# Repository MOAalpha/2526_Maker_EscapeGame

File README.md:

Projet de GHERRAS M.A., dans le cadre de l'option MAKER 2526.
# **<u>EscapeGame</u>**

Ceci est un projet personnel. L'objectif est de créer une boîte avec différentes énigmes, en mettant en oeuvre différentes compétences apprises, entre la Conception Assistée par Ordinateur (CAO) jusqu'à la fabrication d'un PCB.

## Synopsis

*Une épidémie ravage le monde. Personne n'est à l'abri. Environ 10 000 000 de personnes succombent chaque seconde. Le virus possède une forte volatilité et tue en quelques jours. Le docteur Frank MaBoule, après avoir utilisé sa fille comme cobaye,  a créé un remède. Sa fille ayant succombé, il décida de cacher son remède.Sauriez-vous être le héros qui sauvera ~~le monde~~ votre peau ? Voici les épreuves qui vous attendent :*

### 1. FIND A CODE 
Pour ouvrir la première porte, il faut résoudre une énigme très classique consistant à reconstituer une séquence sur un damier de 4x4 symbolisé par 16 écrans.

### 2. DRESS or LESS 

Pour la deuxième porte, l'idée est de vêtir 3 personnages avec le bon chapeau, pull et pentalon, à l'aide de capteurs RFID. Pour cela, une description incomplète sera fournie à travers l'écran principale.

### 3. CHOOSE THE HERO

Parmi les 3 personnages, un seul cache le remède. Vous aurez leur témoignage pour savoir qui possède le remède.

## Matériel (liste actuelle non exhaustive):

> - 1 écran 15cmx10cm tactile (moniteur principale) [de ce type-là](https://www.amazon.fr/Tactile-Fabricant-Bricolage-Internet-%C3%A9lectrique/dp/B0BWNQKWJR)
> - 16 écrans de 4x4 ?
> - Actionneurs pour portes ? 
> - PLA pour les personnages
> - tissu pour les vêtements
> - ~Capteurs RFID miniatures ?~
> - [Capteurs magnétiques, reed switchs](https://www.amazon.fr/Gebildet-interrupteurs-Plastique-Contact-Aimant/dp/B07Z4RR4QV/ref=sr_1_6?dib=eyJ2IjoiMSJ9.kGH2TBV2svDam5SUsecZEp0ydWFLr87Lerqu3hkDXa-I73LrAi6tJurhBRlbuaOspJMU1R2bbn2FAA0ulAMiDROJe-FI64w4Tjx_S1jUe9Khu_sLVSmTS067nG6PzxzhEe5ynbjlwu14H0lsywINTnsO49MUYXsK2D6I_bHxoZ03CqrzpxEMnH7ZNclkzauLTkVpxc65eaC75tjzrhDfIBqrKW-iIr1qnzNfiRqiW8g6QUxy09GzQAjlkQqSTfp91xtdCeA01pv9tRQlohX_FAPPxJ8mOdgauN9amGSbQV0.4Op6Iyob0iHGZqmOrZvQicO9HlkG0YgwPn08NIkEwyQ&dib_tag=se&keywords=reed%2Bswitch&qid=1771235277&sr=8-6&th=1)
> - *A suivre...*

## Planning prévisionnel 

| Séance                  | Action prévue |
|-------------------------|---------------|
| Lundi 16 février 2026   |  Conception des énigmes + Début schématique PCB           |
| Jeudi 19 février 2026   |     Choix des composants(Ecrans, Rasperry Pi/STM) + Suite PCB        |
| Lundi 9 mars 2026       | Début conception mécanique (Plan de la boite, portes, personnages...)              |
| Jeudi 12 mars 2026      |      Découpe laser pour la boîte et premières impressions de pièces         |
| Lundi 16 mars 2026      |    Test PCB        |
| Jeudi 19 mars 2026      |   Setup capteurs RFID + Ecrans principales              |
| Lundi 23 mars 2026      |  Améliorations + Correction             |
| Jeudi 26 mars 2026      |  Code sur STM/Rasberry Pi             |
| Lundi 30 mars 2026      |    Tests / A voir            |
| Jeudi 2 avril 2026      |    A voir            |
| Jeudi 9 avril 2026      |  Possibilité de rajouter des énigmes si tout fonctionne. / Création chatbot pour l'énigme des personnages si le temps le permet.            |
| Lundi 13 avril 2026     |   A voir            |

GANTT : (*IA MADE, for visual*)

```mermaid

gantt
    title Planning du projet (février – avril 2026)
    dateFormat  YYYY-MM-DD
    axisFormat  %d/%m

    section Conception
    Conception des énigmes + schéma PCB         :a1, 2026-02-16, 3d
    Choix composants + suite PCB                :a2, after a1, 3d

    section Mécanique
    Conception mécanique (boîte, portes, persos):b1, 2026-03-09, 4d
    Découpe laser + impressions pièces          :b2, after b1, 3d

    section Électronique
    Test PCB                                    :c1, after a2, 2d
    Setup capteurs RFID + écrans principaux     :c2, after c1, 3d

    section Développement
    Améliorations + corrections                 :d1, after c2, 3d
    Code sur STM / Raspberry Pi                 :d2, after d1, 4d

    section Tests & ajustements
    Tests généraux                              :e1, after d2, 3d
    Ajustements techniques                     :e2, after e1, 3d

    section Extensions (optionnel)
    Ajout d’énigmes / chatbot personnages       :f1, after e2, 4d

    section Final
    Finalisation & préparation soutenance       :g1, after f1, 2d

```

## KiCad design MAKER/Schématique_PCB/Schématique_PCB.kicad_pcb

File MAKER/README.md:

RQ : Remplacement des cartes RFID (16 capteurs) par des touch sensors TTP223 (9)

> *« Ici seront contées les aventures de ce projet. »*

> - **Liste de matériel** :\
      - [Interrupteur Tactile TTP223](https://www.amazon.fr/JZK-modules-tactiles-capacitifs-auto-bloquants/dp/B09VPK9N7F/ref=sr_1_6?dib=eyJ2IjoiMSJ9.8OlufAUh8kHpliZ8zupCCmTH_1LajRCBx3TBxeMsP93xbUSG4nMBz5EggnfvxX5-wFBP-mNZlAdD3oZ_x80vHOl5Eu3p5WBa4hQfzpBYVAvIPwkdTrMa7_UeFh-mwhVQe88JBT1aLw37SmB02eawV-rvWlw8ya8PClwb6dimP2l-XTOxr1rG_YN_8G1GBU_cjgy9zXDspOKH0NJYYGg7HYUNx1oXszeuIKOPoU2a1oKXFQtOdU_Vld4WLojiB3b5yrZtdu84WlLH55zWdur0Hste03VV6Poh6vlHaJ5FiX0.bzc73_ahUhkKb_yN-JHn5xEeCGbjCXaMmTETQ8kozCE&dib_tag=se&keywords=ttp223&qid=1773040746&sr=8-6)\
      - [Capteur Reed (I2L)](https://www.amazon.fr/Gebildet-interrupteurs-Plastique-Contact-Aimant/dp/B07Z4RR4QV/ref=sr_1_6?dib=eyJ2IjoiMSJ9.kGH2TBV2svDam5SUsecZEp0ydWFLr87Lerqu3hkDXa-I73LrAi6tJurhBRlbuaOspJMU1R2bbn2FAA0ulAMiDROJe-FI64w4Tjx_S1jUe9Khu_sLVSmTS067nG6PzxzhEe5ynbjlwu14H0lsywINTnsO49MUYXsK2D6I_bHxoZ03CqrzpxEMnH7ZNclkzauLTkVpxc65eaC75tjzrhDfIBqrKW-iIr1qnzNfiRqiW8g6QUxy09GzQAjlkQqSTfp91xtdCeA01pv9tRQlohX_FAPPxJ8mOdgauN9amGSbQV0.4Op6Iyob0iHGZqmOrZvQicO9HlkG0YgwPn08NIkEwyQ&dib_tag=se&keywords=reed%2Bswitch&qid=1771235277&sr=8-6&th=1 )\
      - [Ecran Tactile](https://www.amazon.fr/Module-daffichage-Tactile-Support-Fonction/dp/B07PKB691V?th=1)

> 1. **Lundi 16 février :** Première séance du projet.
>   - Recherche de composants/solutions pour la 3e énigme
>     - Choix des [reed switch](https://www.amazon.fr/Gebildet-interrupteurs-Plastique-Contact-Aimant/dp/B07Z4RR4QV/ref=sr_1_6?dib=eyJ2IjoiMSJ9.kGH2TBV2svDam5SUsecZEp0ydWFLr87Lerqu3hkDXa-I73LrAi6tJurhBRlbuaOspJMU1R2bbn2FAA0ulAMiDROJe-FI64w4Tjx_S1jUe9Khu_sLVSmTS067nG6PzxzhEe5ynbjlwu14H0lsywINTnsO49MUYXsK2D6I_bHxoZ03CqrzpxEMnH7ZNclkzauLTkVpxc65eaC75tjzrhDfIBqrKW-iIr1qnzNfiRqiW8g6QUxy09GzQAjlkQqSTfp91xtdCeA01pv9tRQlohX_FAPPxJ8mOdgauN9amGSbQV0.4Op6Iyob0iHGZqmOrZvQicO9HlkG0YgwPn08NIkEwyQ&dib_tag=se&keywords=reed%2Bswitch&qid=1771235277&sr=8-6&th=1)
>   - Début de conception [Personnage](https://cad.onshape.com/documents/36c05aa2ce0a4fdcf2218e35/w/67816f6025d3e2feaa42b7d7/e/d2e63ed0c857ded856796908?renderMode=0&uiState=69aeadd01195b52c19ae8e3e)

> 2. **Lundi 9 mars :**
>   - Recherche de composants pour la 1ere énigme : 
>     - Découverte des [interrupteurs tactiles TTP223](https://www.amazon.fr/JZK-modules-tactiles-capacitifs-auto-bloquants/dp/B09VPK9N7F/ref=sr_1_6?dib=eyJ2IjoiMSJ9.8OlufAUh8kHpliZ8zupCCmTH_1LajRCBx3TBxeMsP93xbUSG4nMBz5EggnfvxX5-wFBP-mNZlAdD3oZ_x80vHOl5Eu3p5WBa4hQfzpBYVAvIPwkdTrMa7_UeFh-mwhVQe88JBT1aLw37SmB02eawV-rvWlw8ya8PClwb6dimP2l-XTOxr1rG_YN_8G1GBU_cjgy9zXDspOKH0NJYYGg7HYUNx1oXszeuIKOPoU2a1oKXFQtOdU_Vld4WLojiB3b5yrZtdu84WlLH55zWdur0Hste03VV6Poh6vlHaJ5FiX0.bzc73_ahUhkKb_yN-JHn5xEeCGbjCXaMmTETQ8kozCE&dib_tag=se&keywords=ttp223&qid=1773040746&sr=8-6)
>   - Choix de la [STM32G474RET6](https://www.mouser.fr/ProductDetail/STMicroelectronics/STM32G474RET6?qs=PzGy0jfpSMvUBs7PMTDqlg%3D%3D)
>   - Choix de l'écran : [Affichage LCD TFT Couleur Tactile de 3,2 po.](https://www.amazon.fr/Module-daffichage-Tactile-Support-Fonction/dp/B07PKB691V?th=1)
>   - Recherche code Ecran : [Electrocodeur](https://youtu.be/JoLnnLlXwX0)

> ...
> **Semaine XX : Death time**
> - Impressions des personnages pour la 2e énigme
> - Découpe de la boîte, avec une petite gravure
> - Conception PCB, puis soudure au four
> - Soudure ratée (pâtes soudées entre elles, plus manque d'une lipo Simple)
> - Test avec Nucleo pour l'écran et 2 TTP (fonctionne bien)

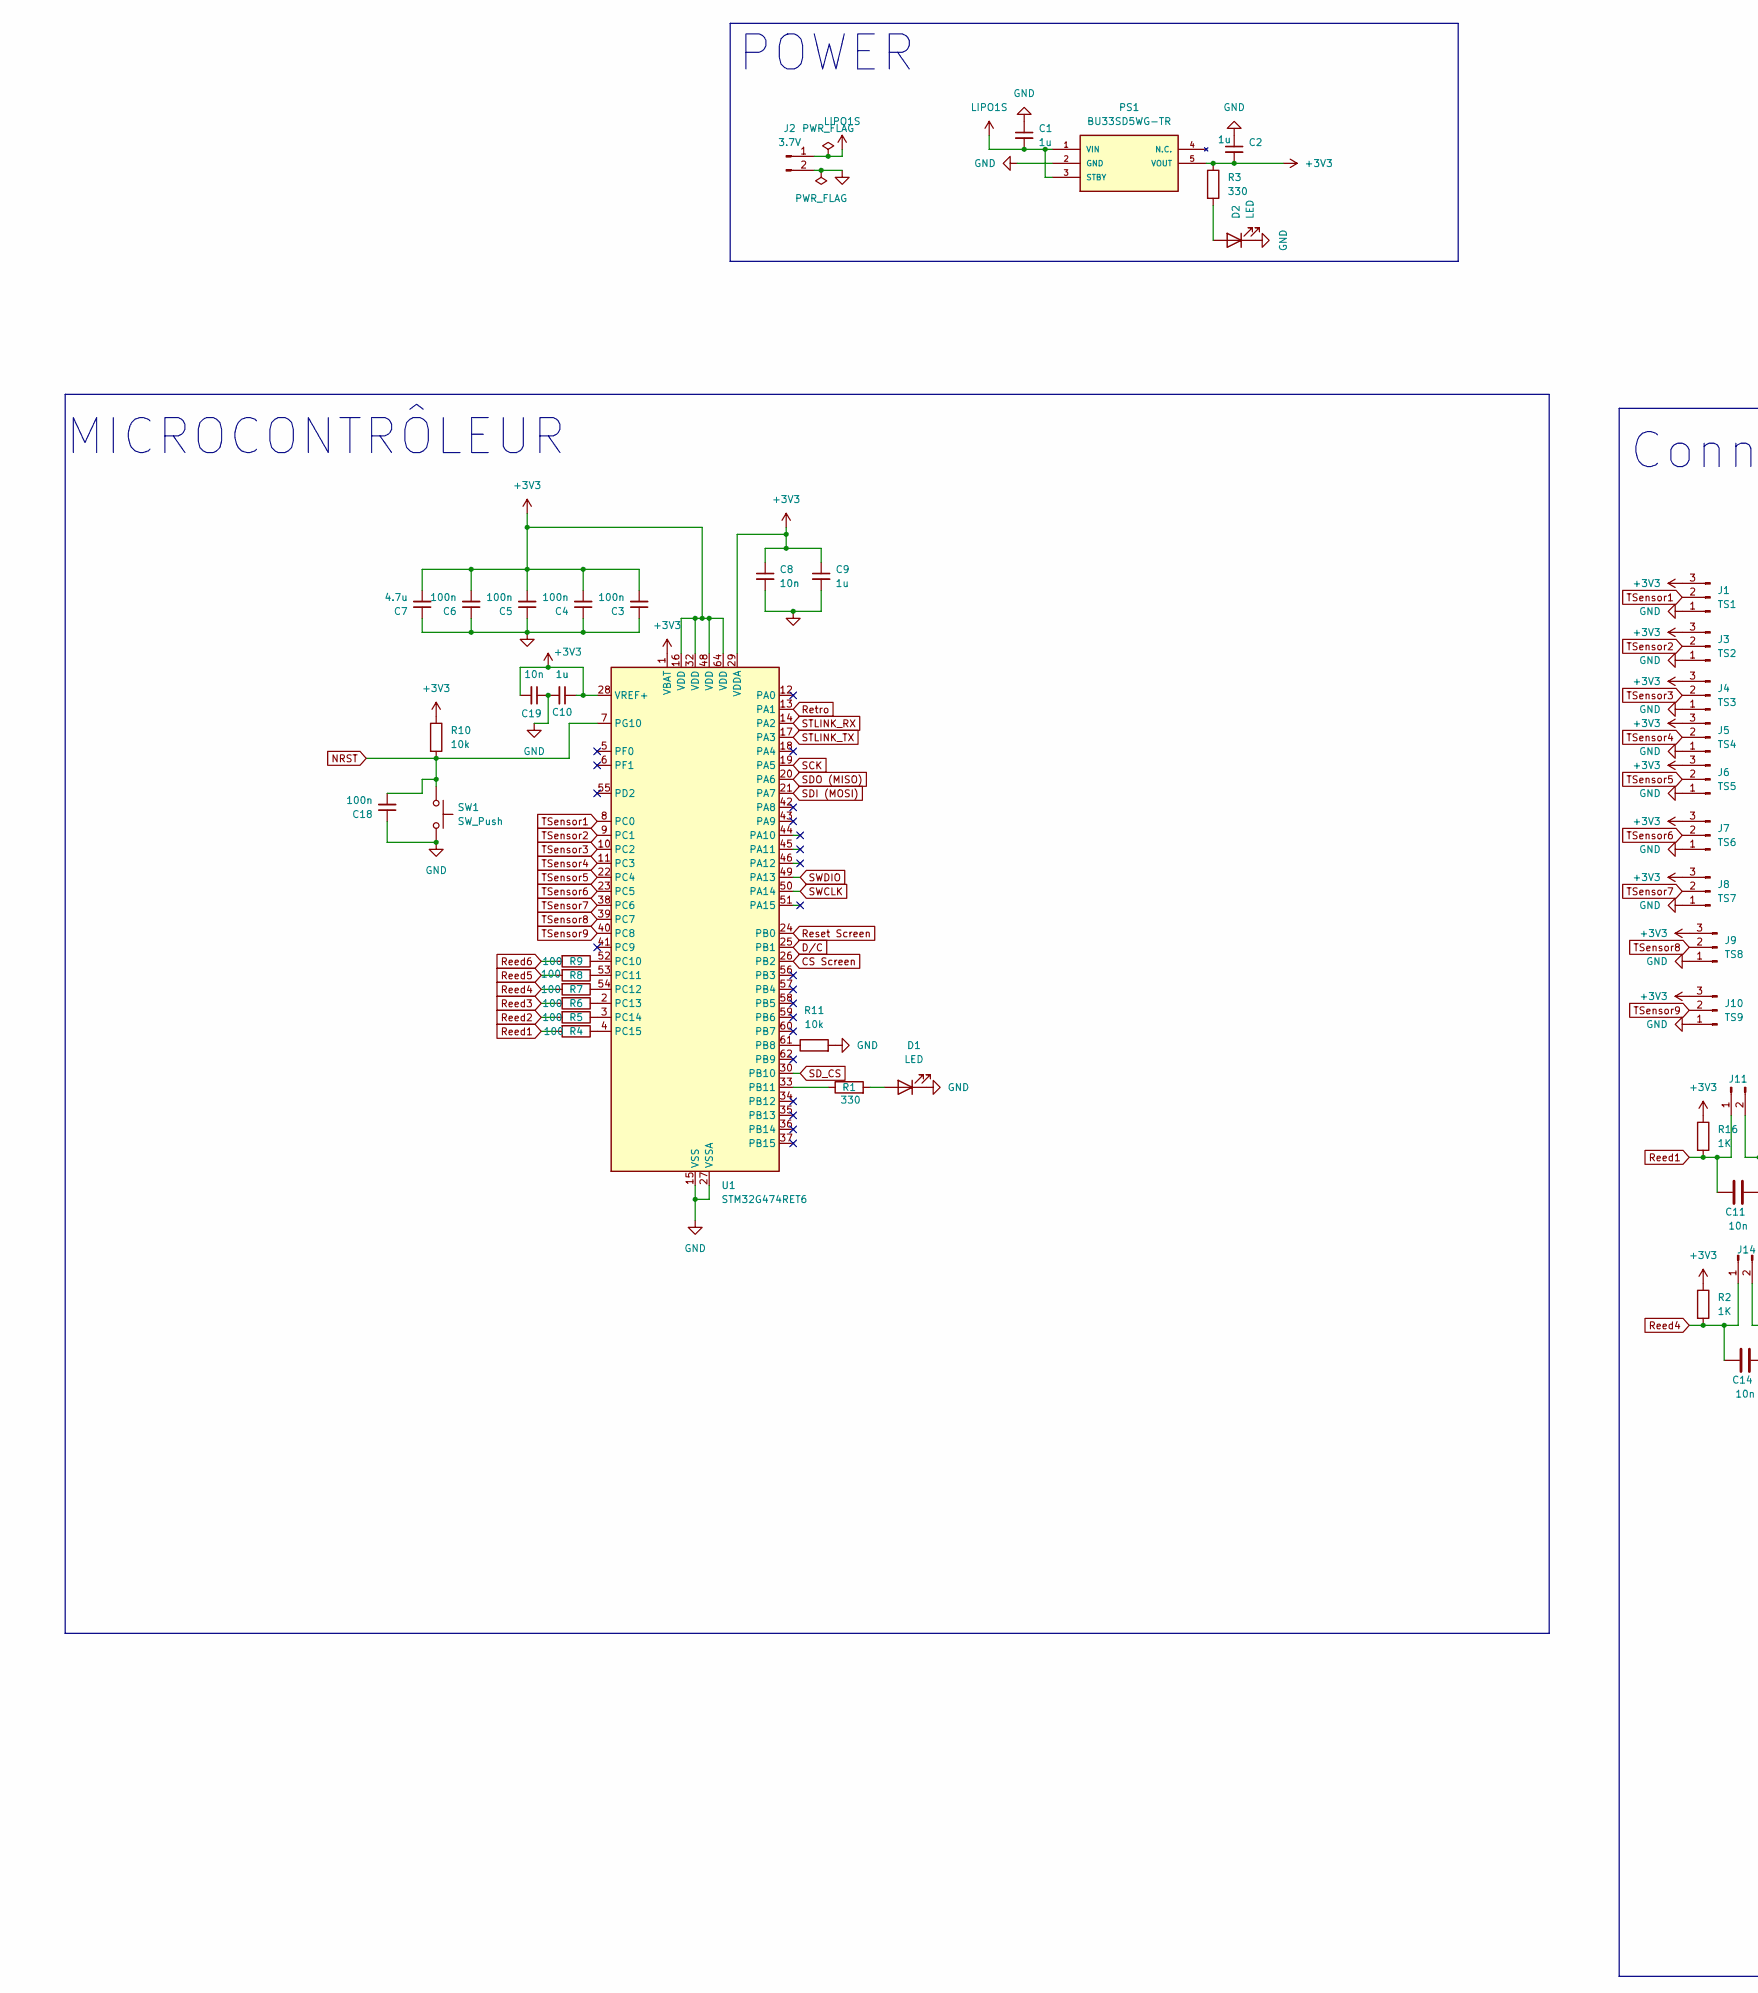
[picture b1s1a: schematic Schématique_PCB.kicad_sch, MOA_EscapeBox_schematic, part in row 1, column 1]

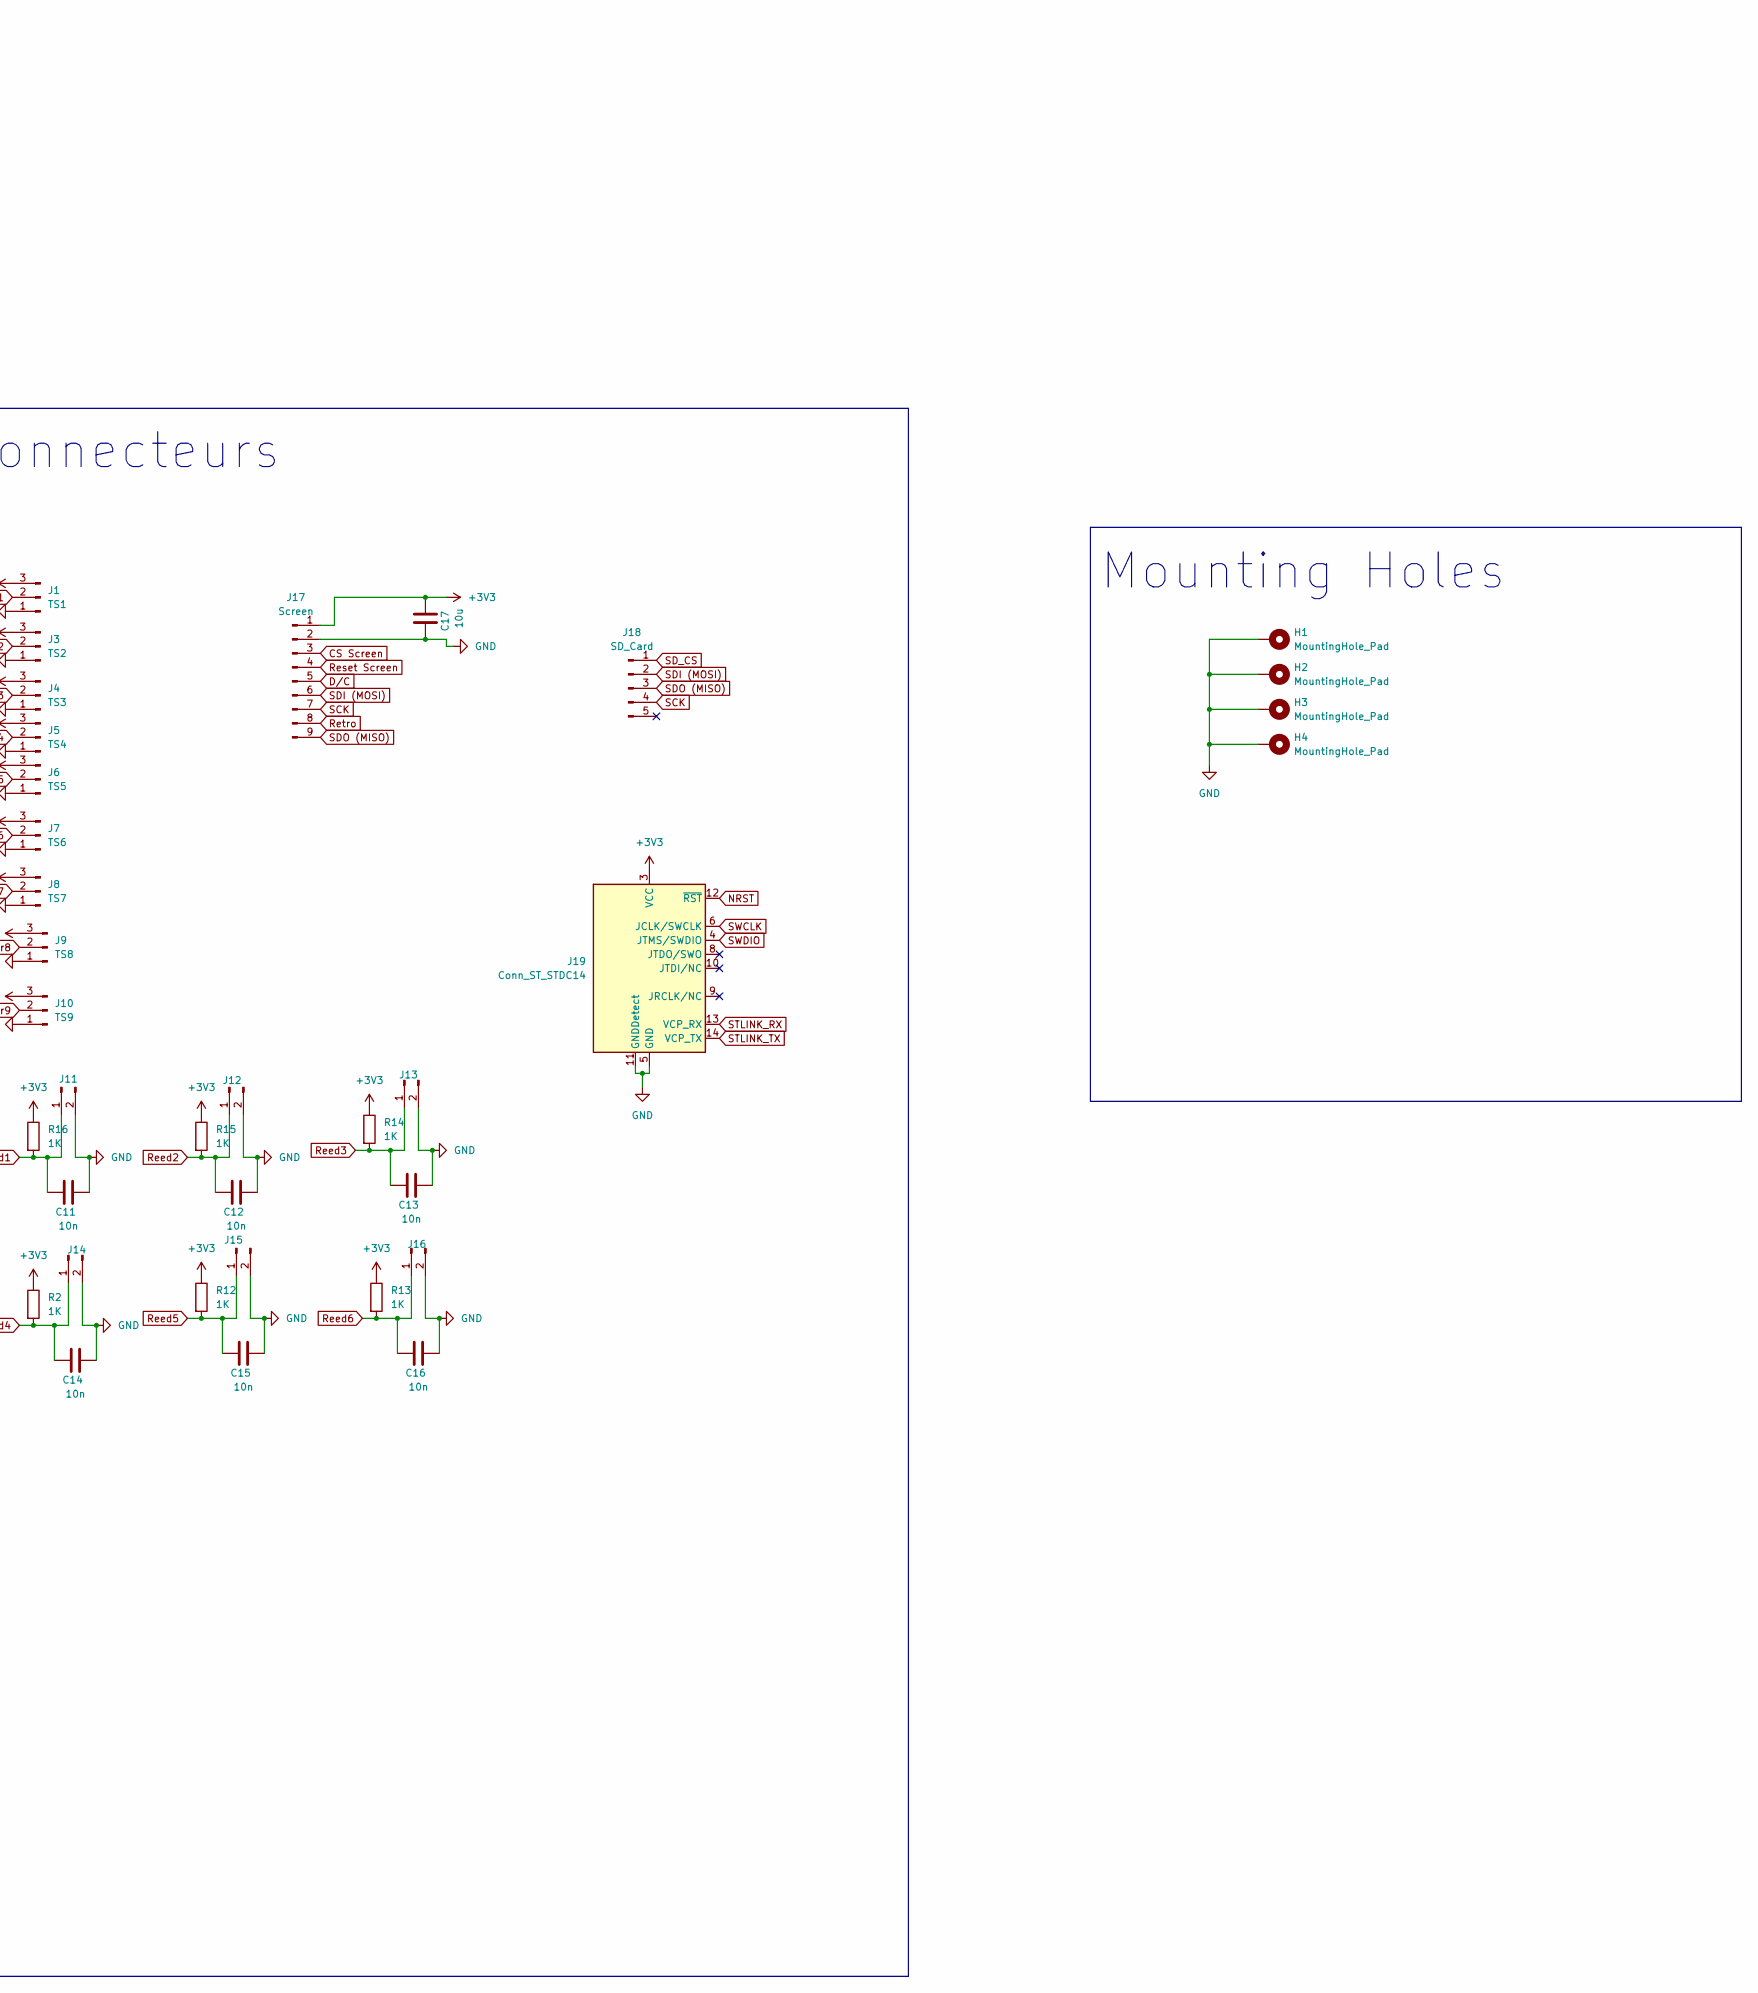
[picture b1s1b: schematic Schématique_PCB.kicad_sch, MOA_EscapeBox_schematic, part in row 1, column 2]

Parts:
C1, C2, C9, C10: 1u; C_0805_2012Metric_Pad1.18x1.45mm_HandSolder
C3, C4, C5, C6, C18: 100n; C_0805_2012Metric_Pad1.18x1.45mm_HandSolder
C7: 4.7u; C_0805_2012Metric_Pad1.18x1.45mm_HandSolder
C8, C11, C12, C13, C14, C15, C16, C19: 10n; C_0805_2012Metric_Pad1.18x1.45mm_HandSolder
C17: 10u; C_0805_2012Metric_Pad1.18x1.45mm_HandSolder
D1, D2: LED; LED_0805_2012Metric_Pad1.15x1.40mm_HandSolder
H1, H2, H3, H4: MountingHole_Pad; MountingHole_3.2mm_M3_DIN965_Pad
J1: TS1; PinHeader_1x03_P2.54mm_Vertical
J2: 3.7V; JST_PH_B2B-PH-K_1x02_P2.00mm_Vertical
J3: TS2; PinHeader_1x03_P2.54mm_Vertical
J4: TS3; PinHeader_1x03_P2.54mm_Vertical
J5: TS4; PinHeader_1x03_P2.54mm_Vertical
J6: TS5; PinHeader_1x03_P2.54mm_Vertical
J7: TS6; PinHeader_1x03_P2.54mm_Vertical
J8: TS7; PinHeader_1x03_P2.54mm_Vertical
J9: TS8; PinHeader_1x03_P2.54mm_Vertical
J10: TS9; PinHeader_1x03_P2.54mm_Vertical
J11, J12, J13, J14, J15, J16: Conn_01x02_Pin; PinHeader_1x02_P2.54mm_Vertical
J17: Screen; PinSocket_1x09_P2.54mm_Vertical
J18: SD_Card; PinSocket_1x05_P2.54mm_Vertical
J19: Conn_ST_STDC14; IDC-Header_2x07_P2.54mm_Vertical
PS1: BU33SD5WG-TR; SOT95P280X125-5N; Mouser_Part_Number 755-BU33SD5WG-TR
R1, R3: 330; R_0805_2012Metric_Pad1.20x1.40mm_HandSolder
R2, R12, R13, R14, R15, R16: 1K; R_0805_2012Metric_Pad1.20x1.40mm_HandSolder
R4, R5, R6, R7, R8, R9: 100; R_0805_2012Metric_Pad1.20x1.40mm_HandSolder
R10, R11: 10k; R_0805_2012Metric_Pad1.20x1.40mm_HandSolder
SW1: SW_Push; SW_SPST_B3U-1000P
U1: STM32G474RET6; LQFP-64_10x10mm_P0.5mm

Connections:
+3V3: C2.2, C3.2, C4.2, C5.2, C6.2, C7.2, C8.1, C9.1, C10.1, C17.2, C19.2, J1.3, J3.3, J4.3, J5.3, J6.3, J7.3, J8.3, J9.3, J10.3, J17.1, J19.3 (VCC), PS1.5 (VOUT), R2.1, R3.1, R10.1, R12.1, R13.1, R14.1, R15.1, R16.1, U1.1 (VBAT), U1.16 (VDD), U1.28 (VREF+), U1.29 (VDDA), U1.32 (VDD), U1.48 (VDD), U1.64 (VDD)
CS Screen: J17.3, U1.26 (PB2)
D/C: J17.5, U1.25 (PB1)
GND: C1.1, C2.1, C3.1, C4.1, C5.1, C6.1, C7.1, C8.2, C9.2, C10.2, C11.2, C12.2, C13.2, C14.2, C15.2, C16.2, C17.1, C18.1, C19.1, D1.1 (K), D2.1 (K), H1.1, H2.1, H3.1, H4.1, J1.1, J2.2, J3.1, J4.1, J5.1, J6.1, J7.1, J8.1, J9.1, J10.1, J11.2, J12.2, J13.2, J14.2, J15.2, J16.2, J17.2, J19.5 (GND), J19.7 (GND), J19.11 (GNDDetect), PS1.2 (GND), R11.2, SW1.2, U1.15 (VSS), U1.27 (VSSA), U1.31 (VSS), U1.47 (VSS), U1.63 (VSS)
LIPO1S: C1.2, J2.1, PS1.1 (VIN), PS1.3 (STBY)
NRST: C18.2, J19.12 (~RST), R10.2, SW1.1, U1.7 (PG10)
unnamed: D1.2 (A), R1.2
unnamed: D2.2 (A), R3.2
unnamed: R11.1, U1.61 (PB8)
unnamed: R1.1, U1.33 (PB11)
unnamed: R9.1, U1.52 (PC10)
unnamed: R8.1, U1.53 (PC11)
unnamed: R7.1, U1.54 (PC12)
unnamed: R6.1, U1.2 (PC13)
unnamed: R5.1, U1.3 (PC14)
unnamed: R4.1, U1.4 (PC15)
Reed1: C11.1, J11.1, R4.2, R16.2
Reed2: C12.1, J12.1, R5.2, R15.2
Reed3: C13.1, J13.1, R6.2, R14.2
Reed4: C14.1, J14.1, R2.2, R7.2
Reed5: C15.1, J15.1, R8.2, R12.2
Reed6: C16.1, J16.1, R9.2, R13.2
Reset Screen: J17.4, U1.24 (PB0)
Retro: J17.8, U1.13 (PA1)
SCK: J17.7, J18.4, U1.19 (PA5)
SDI (MOSI): J17.6, J18.2, U1.21 (PA7)
SDO (MISO): J17.9, J18.3, U1.20 (PA6)
SD_CS: J18.1, U1.30 (PB10)
STLINK_RX: J19.13 (VCP_RX), U1.14 (PA2)
STLINK_TX: J19.14 (VCP_TX), U1.17 (PA3)
SWCLK: J19.6 (JCLK/SWCLK), U1.50 (PA14)
SWDIO: J19.4 (JTMS/SWDIO), U1.49 (PA13)
TSensor1: J1.2, U1.8 (PC0)
TSensor2: J3.2, U1.9 (PC1)
TSensor3: J4.2, U1.10 (PC2)
TSensor4: J5.2, U1.11 (PC3)
TSensor5: J6.2, U1.22 (PC4)
TSensor6: J7.2, U1.23 (PC5)
TSensor7: J8.2, U1.38 (PC6)
TSensor8: J9.2, U1.39 (PC7)
TSensor9: J10.2, U1.40 (PC8)

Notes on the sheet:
POWER
Mounting Holes
Connecteurs
MICROCONTRÔLEUR

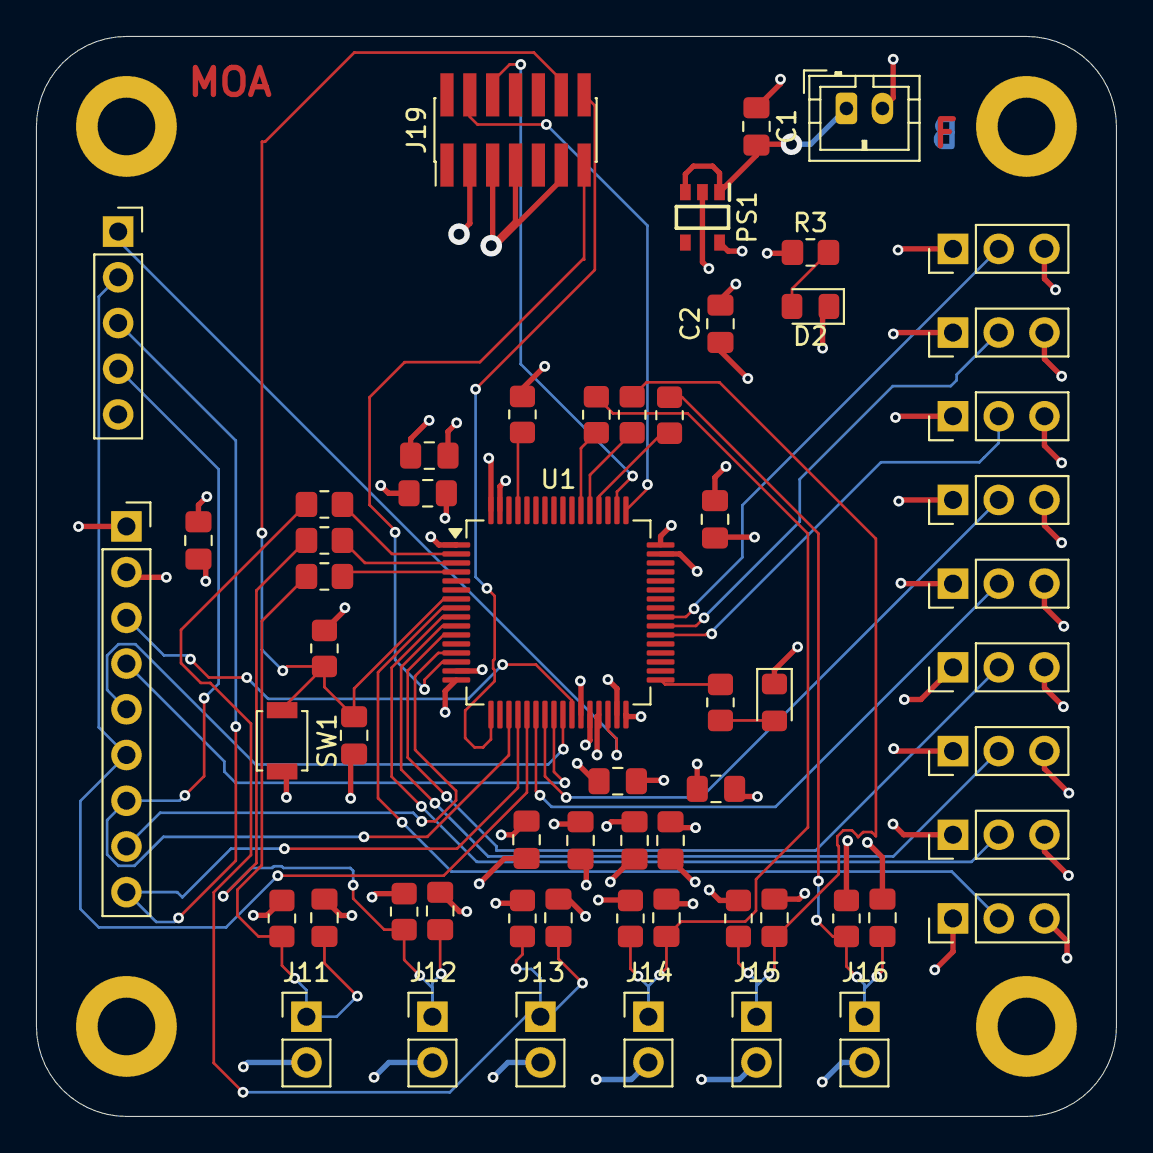
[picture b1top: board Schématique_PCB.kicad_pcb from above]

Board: 4 copper layers, 60.0 x 60.0 mm, 63 parts (0 on the bottom side), 41 nets.

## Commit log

2026-01-18 Ajout readme
2026-01-18 Insert Gantt chart for project planning
    Added a Gantt chart to the project planning section.
2026-01-18 Fix formatting of code block in README
2026-01-18 Include Gantt chart in README for project timeline
    Added Gantt chart section for project planning.
2026-01-19 Update README with my name
    Added project description for GHERRAS M.A.
2026-01-21 Add screenshot link for Onshape elements
2026-01-21 Captures Ecran CAO + Version PDF
2026-01-21 Update README with Onshape screenshots
    Added screenshots of various elements created on Onshape.
2026-02-16 Update README with magnetic sensors link and remove RFID
2026-03-09 Mise à niveau git
2026-03-09 Fix pb
2026-03-09 Réorganisation du git
2026-03-09 Réorganisation fichiers Kicad
2026-03-09 Journal de Bord
2026-03-09 Update README with link to reed switch
    Added a link to the reed switch in the README.
2026-03-09 "Update suppression de fichiers"
2026-03-09 Suppression fichier étrange
2026-03-09 Ajout readme pour TEST
2026-03-09 Revise README with project updates and component links
    Updated the project timeline and added links to components.
2026-03-09 Update README with additional components and details
2026-04-02 MAJ PCB 4 Couches
2026-04-13 code test Ecran nucléo
2026-04-13 MAJ Prog de test avec Nb aléatoire
2026-05-03 Ajout fichiers maker
2026-05-03 Rename WhatsApp Image 2026-05-03 at 20.06.13.jpeg to batterie.jpeg
2026-05-03 Rename WhatsApp Image 2026-05-03 at 20.06.02.jpeg to USELESS_BOX
2026-05-05 MAJ Ecran avec 2 boutons
2026-05-05 Reorganisation des fichiers + MAJ journal de bord
2026-05-05 Reorganisation fichiers 2
2026-05-05 Update README with sensor replacement details
    Added a note about replacing RFID cards with TTP223 touch sensors and updated the material list.
2026-05-05 Rename WhatsApp Image 2026-05-03 at 20.06.13.jpeg to Batterie2S1P.jpeg
